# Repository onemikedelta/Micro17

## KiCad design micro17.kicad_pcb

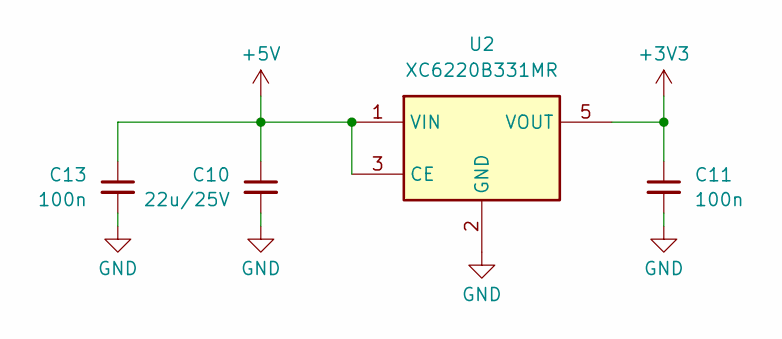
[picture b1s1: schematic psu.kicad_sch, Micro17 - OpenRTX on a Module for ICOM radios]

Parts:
C10: 22u/25V; C_0805_2012Metric; MPN C45783; LCSC C45783
C11, C13: 100n; C_0402_1005Metric; MPN C56392; LCSC C56392
U2: XC6220B331MR; SOT-23-5; MPN C3040644; LCSC C3040644

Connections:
+3V3: C11.1, U2.5 (VOUT); also elsewhere on the board
+5V: C10.1, C13.1, U2.1 (VIN), U2.3 (CE); also elsewhere on the board
GND: C10.2, C11.2, C13.2, U2.2 (GND); also elsewhere on the board

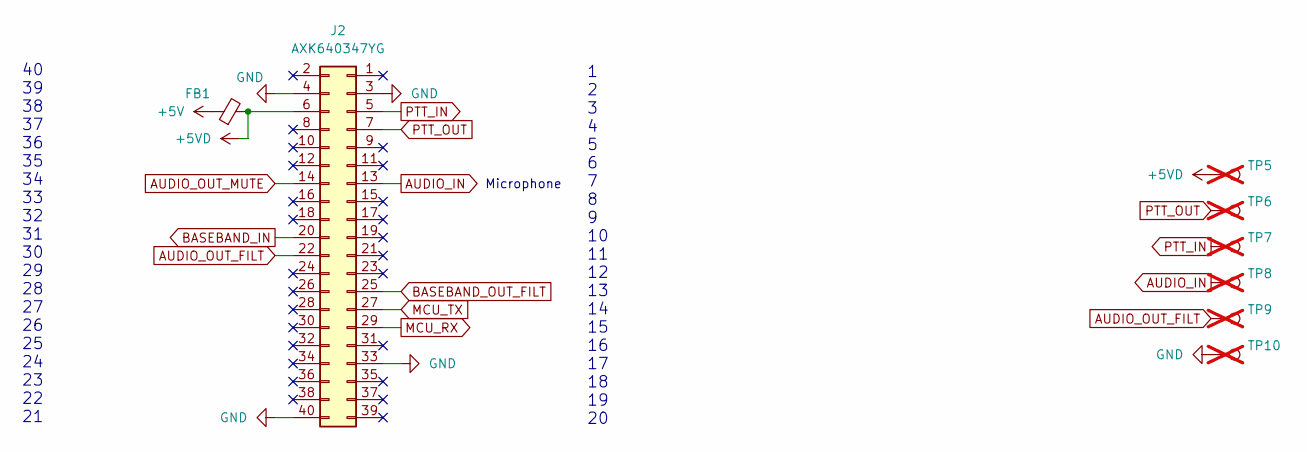
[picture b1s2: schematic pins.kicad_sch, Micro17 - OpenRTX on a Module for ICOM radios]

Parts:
FB1: FerriteBead_Small; L_0603_1608Metric_Pad1.05x0.95mm_HandSolder; MPN C2971885; LCSC C2971885
J2: AXK640347YG; MPN C2936870; LCSC C2936870
TP5, TP6, TP7, TP8, TP9, TP10: GP; TestPoint_Pad_D1.0mm; not fitted

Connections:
+5V: FB1.1; also elsewhere on the board
+5VD: FB1.2, J2.6, TP5.1
AUDIO_IN: J2.13, TP8.1; also elsewhere on the board
AUDIO_OUT_FILT: J2.22, TP9.1; also elsewhere on the board
AUDIO_OUT_MUTE: J2.14; also elsewhere on the board
BASEBAND_IN: J2.20; also elsewhere on the board
BASEBAND_OUT_FILT: J2.25; also elsewhere on the board
GND: J2.3, J2.4, J2.33, J2.40, TP10.1; also elsewhere on the board
MCU_RX: J2.29; also elsewhere on the board
MCU_TX: J2.27; also elsewhere on the board
PTT_IN: J2.5, TP7.1; also elsewhere on the board
PTT_OUT: J2.7, TP6.1; also elsewhere on the board

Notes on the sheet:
Microphone
40 39 38 37 36 35 34 33 32 31 30 29 28 27 26 25 24 23 22 21
1 2 3 4 5 6 7 8 9 10 11 12 13 14 15 16 17 18 19 20

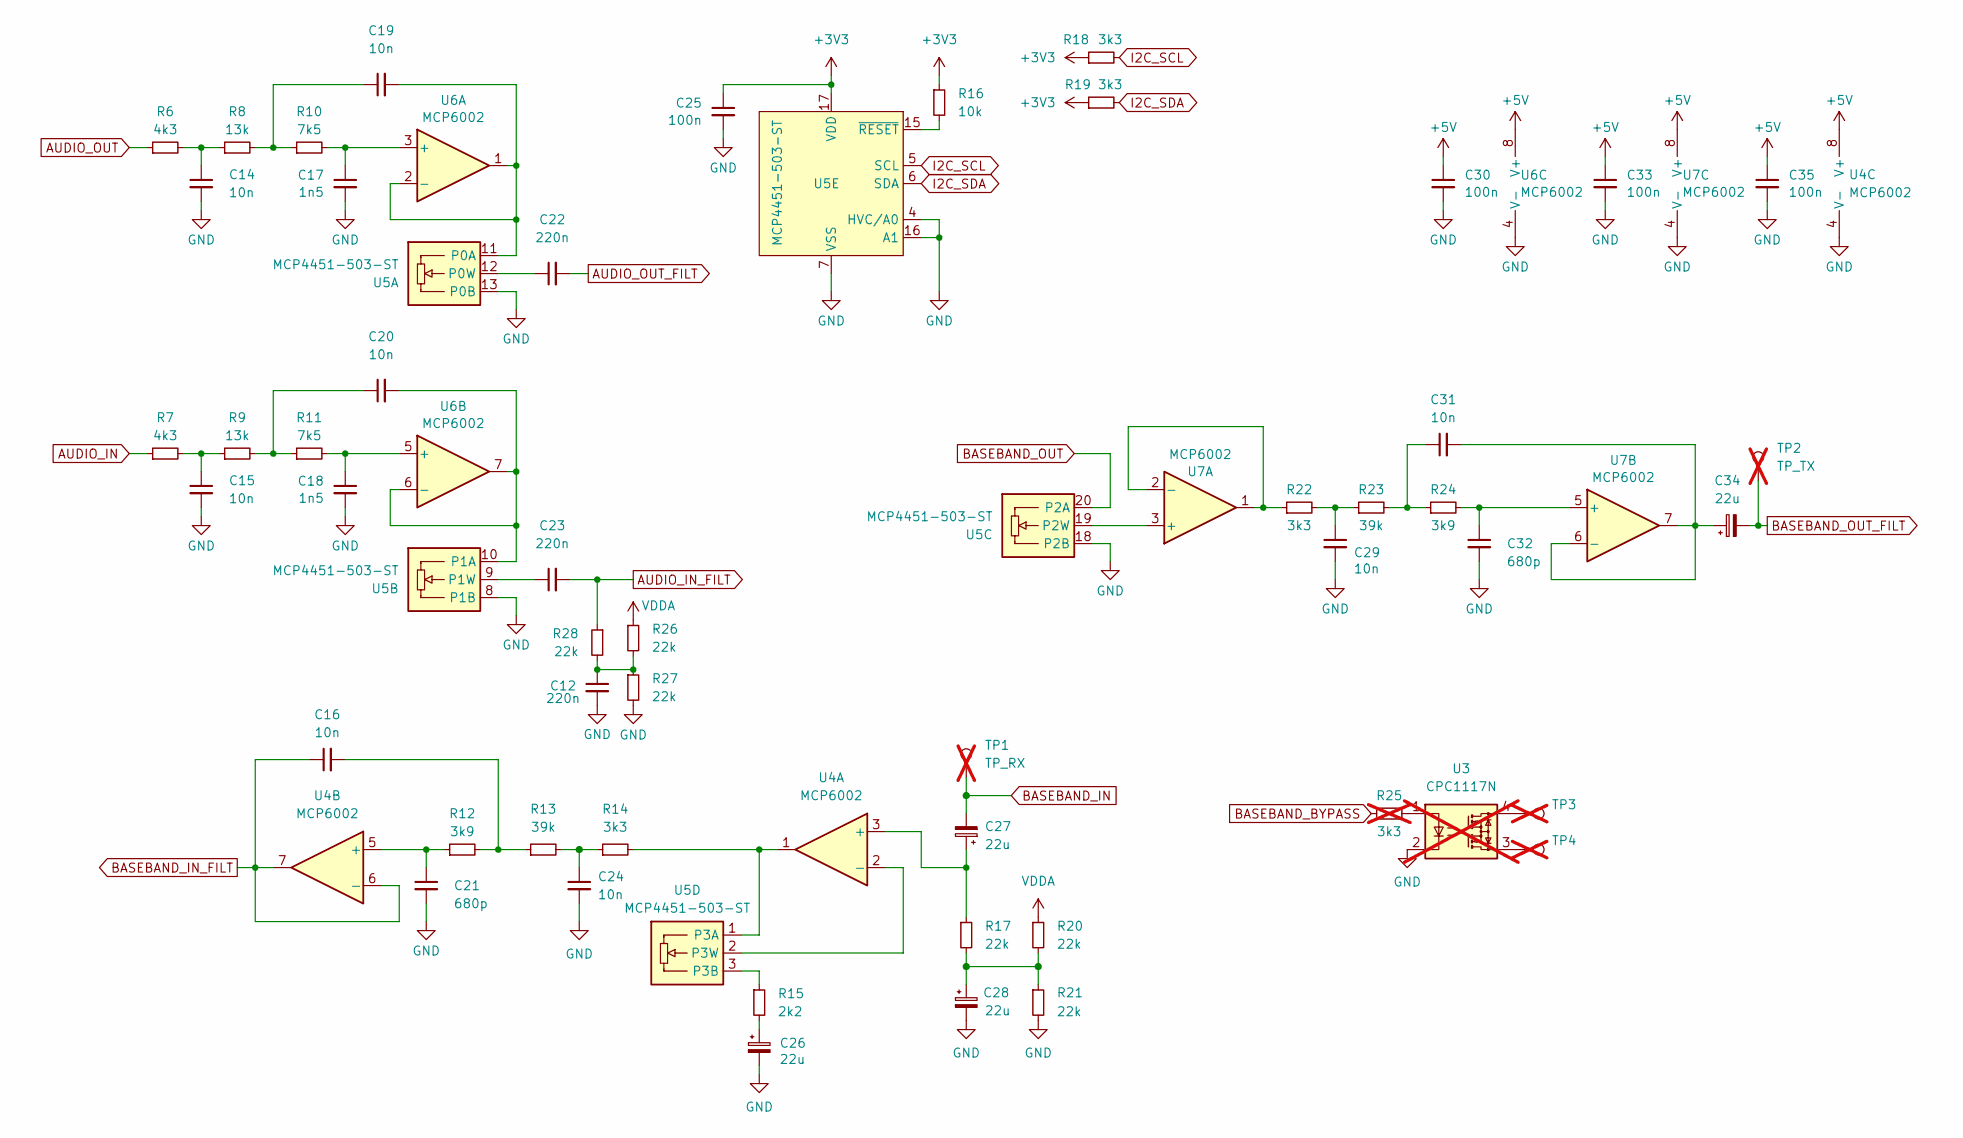
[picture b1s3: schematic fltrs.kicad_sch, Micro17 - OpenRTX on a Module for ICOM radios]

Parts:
C12, C22, C23: 220n; C_0402_1005Metric; MPN C192432; LCSC C192432
C14, C15, C16, C19, C20, C24, C29, C31: 10n; C_0402_1005Metric; MPN C60133; LCSC C60133
C17, C18: 1n5; C_0402_1005Metric; MPN C284989; LCSC C284989
C21, C32: 680p; C_0402_1005Metric; MPN C1541; LCSC C1541
C25, C30, C33, C35: 100n; C_0402_1005Metric; MPN C56392; LCSC C56392
C26, C27, C28, C34: 22u; CP_EIA-3216-18_Kemet-A; MPN C118989; LCSC C118989
R6, R7: 4k3; R_0402_1005Metric; MPN C25899; LCSC C25899
R8, R9: 13k; R_0402_1005Metric; MPN C25754; LCSC C25754
R10, R11: 7k5; R_0402_1005Metric; MPN C2960875; LCSC C2960875
R12: 3k9; R_0402_1005Metric; MPN C3015806; LCSC C3015806
R13, R23: 39k; R_0402_1005Metric; MPN C25783; LCSC C25783
R14, R18, R19, R22: 3k3; R_0402_1005Metric; MPN C25890; LCSC C25890
R15: 2k2; R_0402_1005Metric; MPN C102890; LCSC C102890
R16: 10k; R_0402_1005Metric; MPN C102749; LCSC C102749
R17, R20, R21, R26, R27, R28: 22k; R_0402_1005Metric; MPN C2909337; LCSC C2909337
R24: 3k9; R_0603_1608Metric; MPN C23018; LCSC C23018
R25: 3k3; R_0402_1005Metric; LCSC C25890; not fitted
TP1: TP_RX; TestPoint_Pad_D1.0mm; not fitted
TP2: TP_TX; TestPoint_Pad_D1.0mm; not fitted
TP3, TP4: GP; TestPoint_Pad_D1.0mm; not fitted
U3: CPC1117N; SOP-4_3.8x4.1mm_P2.54mm; not fitted
U4, U6, U7: MCP6002; DFN-8-1EP_3x2mm_P0.5mm_EP1.75x1.45mm; MPN C623660; LCSC C623660
U5: MCP4451-503-ST; TSSOP-20_4.4x6.5mm_P0.65mm; MPN C627257; LCSC C627257

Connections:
+3V3: C25.1, R16.1, R18.1, R19.1, U5.17 (VDD); also elsewhere on the board
+5V: C30.1, C33.1, C35.1, U4.8 (V+), U6.8 (V+), U7.8 (V+); also elsewhere on the board
AUDIO_IN: R7.1; also elsewhere on the board
AUDIO_IN_FILT: C23.2, R28.1; also elsewhere on the board
AUDIO_OUT: R6.1; also elsewhere on the board
AUDIO_OUT_FILT: C22.2; also elsewhere on the board
BASEBAND_BYPASS: R25.1; also elsewhere on the board
BASEBAND_IN: C27.2, TP1.1; also elsewhere on the board
BASEBAND_IN_FILT: C16.1, U4.6 (-), U4.7; also elsewhere on the board
BASEBAND_OUT: U5.20 (P2A); also elsewhere on the board
BASEBAND_OUT_FILT: C34.2, TP2.1; also elsewhere on the board
GND: C12.2, C14.2, C15.2, C17.2, C18.2, C21.2, C24.2, C25.2, C26.2, C28.2, C29.2, C30.2, C32.2, C33.2, C35.2, R21.2, R27.2, U3.2, U4.4 (V-), U4.9 (V-), U5.4 (HVC/A0), U5.7 (VSS), U5.8 (P1B), U5.13 (P0B), U5.16 (A1), U5.18 (P2B), U6.4 (V-), U6.9 (V-), U7.4 (V-), U7.9 (V-); also elsewhere on the board
I2C_SCL: R18.2, U5.5 (SCL); also elsewhere on the board
I2C_SDA: R19.2, U5.6 (SDA); also elsewhere on the board
unnamed: C12.1, R26.2, R27.1, R28.2
unnamed: C14.1, R6.2, R8.1
unnamed: C15.1, R7.2, R9.1
unnamed: C16.2, R12.2, R13.1
unnamed: C19.1, R8.2, R10.1
unnamed: C20.1, R9.2, R11.1
unnamed: C24.1, R13.2, R14.1
unnamed: C26.1, R15.2
unnamed: C28.1, R17.2, R20.2, R21.1
unnamed: C29.1, R22.2, R23.1
unnamed: C31.1, R23.2, R24.1
unnamed: R25.2, U3.1
unnamed: TP3.1, U3.4
unnamed: TP4.1, U3.3
unnamed: C27.1, R17.1, U4.3 (+)
unnamed: U4.2 (-), U5.2 (P3W)
unnamed: C21.1, R12.1, U4.5 (+)
unnamed: C19.2, U5.11 (P0A), U6.1, U6.2 (-)
unnamed: C22.1, U5.12 (P0W)
unnamed: C20.2, U5.10 (P1A), U6.6 (-), U6.7
unnamed: C23.1, U5.9 (P1W)
unnamed: U5.19 (P2W), U7.3 (+)
unnamed: R14.2, U4.1, U5.1 (P3A)
unnamed: R15.1, U5.3 (P3B)
unnamed: R16.2, U5.15 (~RESET)
unnamed: C17.1, R10.2, U6.3 (+)
unnamed: C18.1, R11.2, U6.5 (+)
unnamed: R22.1, U7.1, U7.2 (-)
unnamed: C32.1, R24.2, U7.5 (+)
unnamed: C31.2, C34.1, U7.6 (-), U7.7
VDDA: R20.1, R26.1; also elsewhere on the board

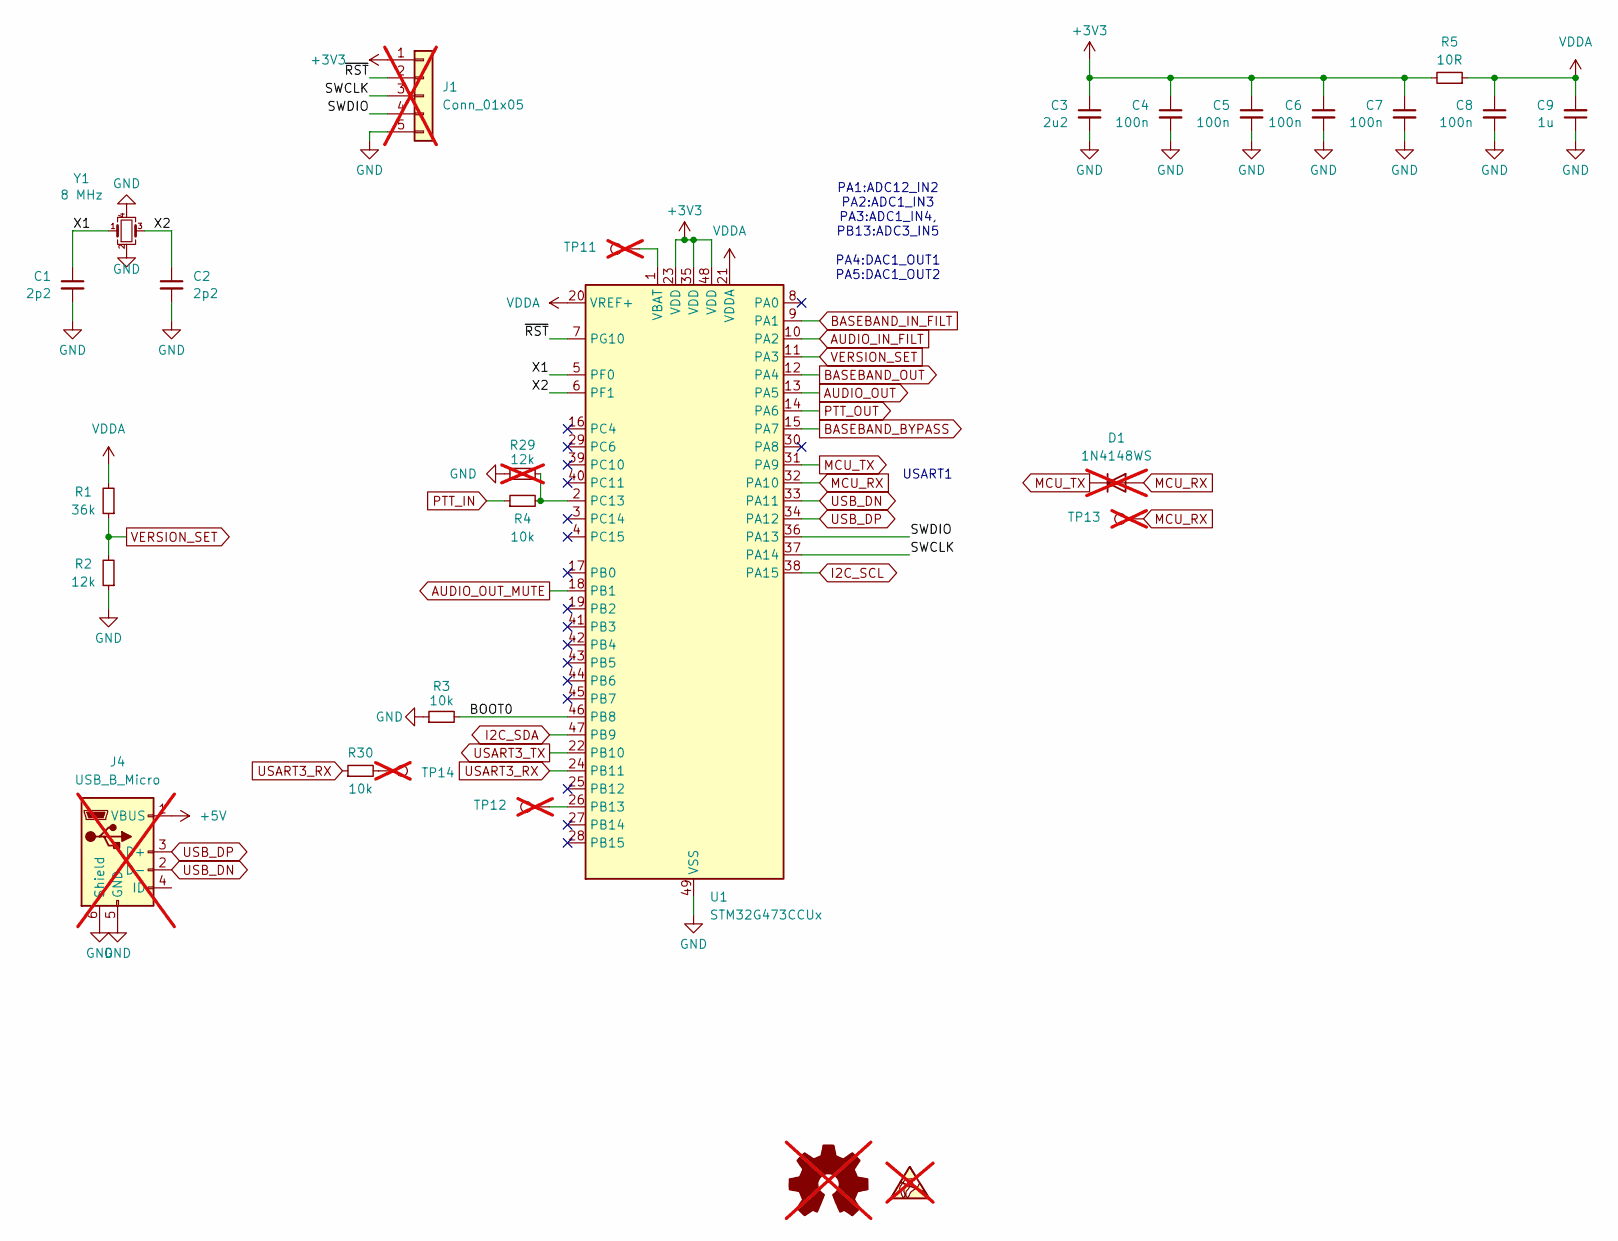
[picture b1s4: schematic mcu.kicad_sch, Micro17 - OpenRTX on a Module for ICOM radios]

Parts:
C1, C2: 2p2; C_0402_1005Metric; MPN C1559; LCSC C1559
C3: 2u2; C_0402_1005Metric; MPN C170151; LCSC C170151
C4, C5, C6, C7, C8: 100n; C_0402_1005Metric; MPN C56392; LCSC C56392
C9: 1u; C_0402_1005Metric; MPN C29266; LCSC C29266
D1: 1N4148WS; D_SOD-323; not fitted
J1: Conn_01x05; Harwin_M20-89005xx_1x05_P2.54mm_Horizontal; not fitted
J4: USB_B_Micro; USB_Micro-B_Molex_47346-0001; not fitted
R1: 36k; R_0402_1005Metric; MPN C4354982; LCSC C4354982
R2: 12k; R_0402_1005Metric; MPN C25752; LCSC C25752
R3, R4, R30: 10k; R_0402_1005Metric; MPN C102749; LCSC C102749
R5: 10R; R_0402_1005Metric; MPN C854481; LCSC C854481
R29: 12k; R_0402_1005Metric; MPN C25752; LCSC C25752; not fitted
SYM1: SYM_ESD_Small; ESD-Logo_6.6x6mm_SilkScreen; not fitted
SYM2: Logo_Open_Hardware_Small; OSHW-Logo_5.7x6mm_SilkScreen; not fitted
TP11, TP12, TP13, TP14: GP; TestPoint_Pad_D1.0mm; not fitted
U1: STM32G473CCUx; QFN-48-1EP_7x7mm_P0.5mm_EP5.6x5.6mm; MPN C1342773; LCSC C1342773
Y1: 8 MHz; Crystal_SMD_3225-4Pin_3.2x2.5mm; MPN C5308002; LCSC C5308002

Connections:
+3V3: C3.1, C4.1, C5.1, C6.1, C7.1, J1.1, R5.2, U1.23 (VDD), U1.35 (VDD), U1.48 (VDD); also elsewhere on the board
+5V: J4.1 (VBUS); also elsewhere on the board
/MCU/BOOT0: R3.2, U1.46 (PB8)
/MCU/SWCLK: J1.3, U1.37 (PA14)
/MCU/SWDIO: J1.4, U1.36 (PA13)
/MCU/X1: C1.1, U1.5 (PF0), Y1.1
/MCU/X2: C2.1, U1.6 (PF1), Y1.3
/MCU/~RST: J1.2, U1.7 (PG10)
AUDIO_IN_FILT: U1.10 (PA2); also elsewhere on the board
AUDIO_OUT: U1.13 (PA5); also elsewhere on the board
AUDIO_OUT_MUTE: U1.18 (PB1); also elsewhere on the board
BASEBAND_BYPASS: U1.15 (PA7); also elsewhere on the board
BASEBAND_IN_FILT: U1.9 (PA1); also elsewhere on the board
BASEBAND_OUT: U1.12 (PA4); also elsewhere on the board
GND: C1.2, C2.2, C3.2, C4.2, C5.2, C6.2, C7.2, C8.2, C9.1, J1.5, J4.5 (GND), J4.6 (Shield), R2.1, R3.1, R29.1, U1.49 (VSS), Y1.2, Y1.4; also elsewhere on the board
I2C_SCL: U1.38 (PA15); also elsewhere on the board
I2C_SDA: U1.47 (PB9); also elsewhere on the board
MCU_RX: D1.2 (A), TP13.1, U1.32 (PA10); also elsewhere on the board
MCU_TX: D1.1 (K), U1.31 (PA9); also elsewhere on the board
unnamed: R30.2, TP14.1
unnamed: TP12.1, U1.26 (PB13)
unnamed: R4.2, R29.2, U1.2 (PC13)
unnamed: TP11.1, U1.1 (VBAT)
PTT_IN: R4.1; also elsewhere on the board
PTT_OUT: U1.14 (PA6); also elsewhere on the board
USART3_RX: R30.1, U1.24 (PB11)
USART3_TX: U1.22 (PB10)
USB_DN: J4.2 (D-), U1.33 (PA11)
USB_DP: J4.3 (D+), U1.34 (PA12)
VDDA: C8.1, C9.2, R1.2, R5.1, U1.20 (VREF+), U1.21 (VDDA); also elsewhere on the board
VERSION_SET: R1.1, R2.2, U1.11 (PA3)

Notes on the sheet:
USART1
PA1:ADC12_IN2 PA2:ADC1_IN3 PA3:ADC1_IN4, PB13:ADC3_IN5 PA4:DAC1_OUT1 PA5:DAC1_OUT2

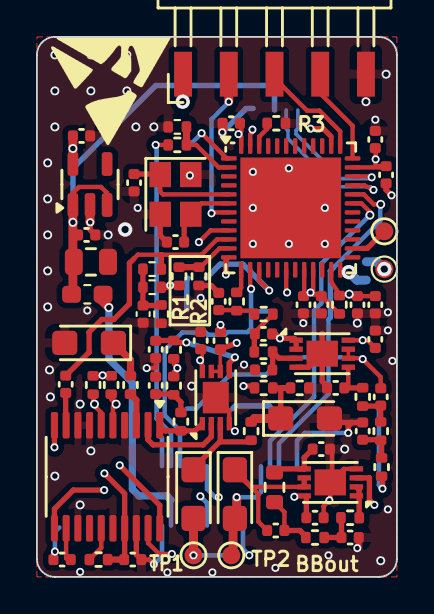
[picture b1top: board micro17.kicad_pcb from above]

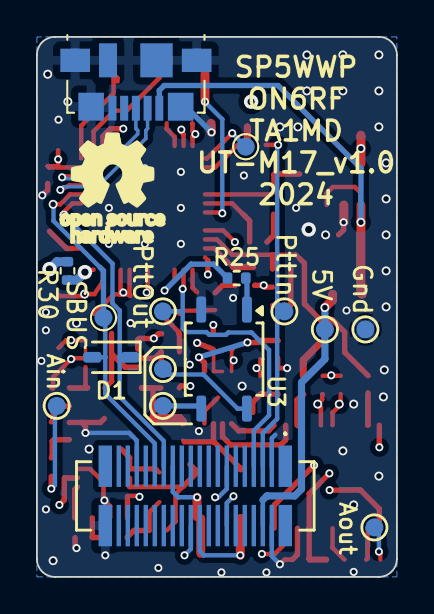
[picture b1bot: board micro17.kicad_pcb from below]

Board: 4 copper layers, 20.0 x 30.0 mm, 94 parts (17 on the bottom side), 65 nets.

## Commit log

2024-03-06 initial commit, not complete.
2024-03-10 PCB shape is created. Most of routing done.
    Todo: assign pins for radio control signals.
2024-03-11 end of day commit
2024-04-02 V1.0 Final touch
2024-04-04 date updated
2024-09-10 VREF+ connected to VDDA
